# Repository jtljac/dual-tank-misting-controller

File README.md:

A circuit board design and ESPHome script for a control board responsible for a misting system for two tanks.  
A route from the pump to each tank can be enabled using solenoids attched to their labelled terminals. Powered terminals
will be indicated by an indicator LED, including when the pump is powered.

There are also a header for a Dallas 1-Wire DS18b20 waterproof temperature sensor for measuring the temperature of the 
water Tank, and a header for a HC-SR04 ultrasonic Distance sensor for use as a water level indicator. The HC-SR04 header
has an associate voltage selector header as they're supposed to be 5v but my cheap ones overheated above 3v3.

The board is powered using a 24V DC Barrel Jack and powers the pump and solenoids directly. This design has sized 
components and traces for 3A, which is generous for the required current for the ESP, pump, and two solenoids.

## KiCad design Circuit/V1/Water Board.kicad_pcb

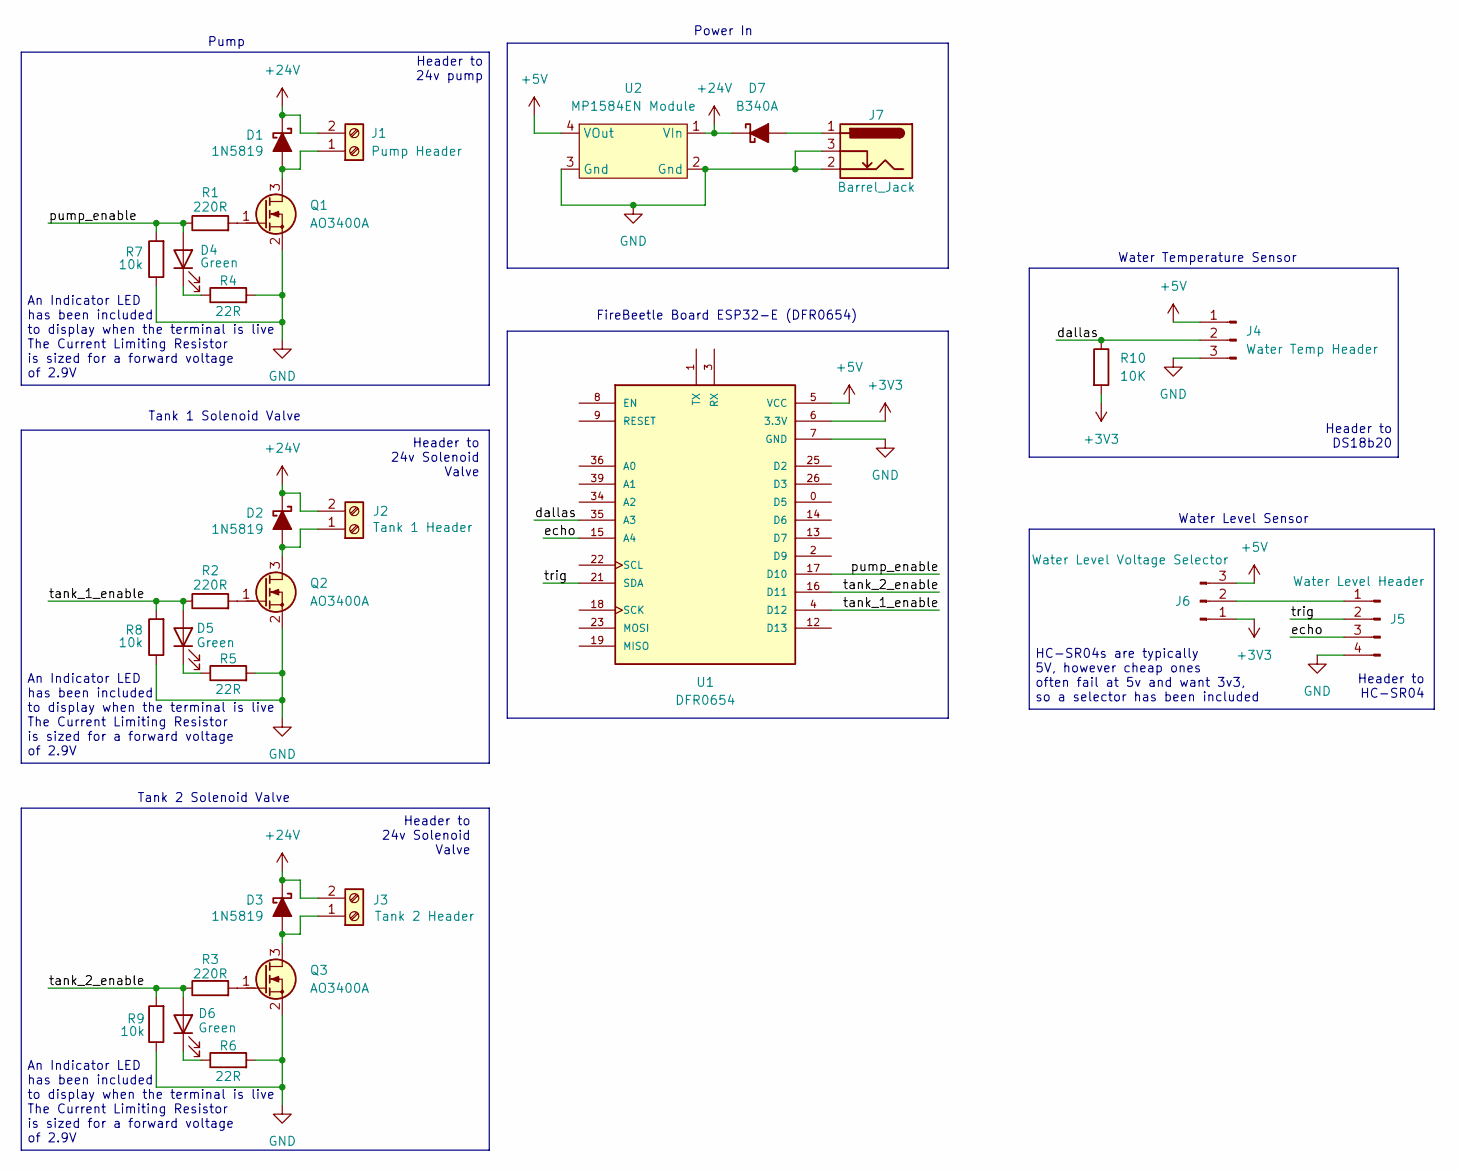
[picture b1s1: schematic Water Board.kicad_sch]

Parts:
D1, D2, D3: 1N5819; D_SOD-123
D4, D5, D6: Green; LED_0805_2012Metric_Pad1.15x1.40mm_HandSolder
D7: B340A; D_SMA_BigPads
J1: Pump Header; TerminalBlock_MAX_MX127-5.0-02P_1x02_P5.00mm
J2: Tank 1 Header; TerminalBlock_MAX_MX127-5.0-02P_1x02_P5.00mm
J3: Tank 2 Header; TerminalBlock_MAX_MX127-5.0-02P_1x02_P5.00mm
J4: Water Temp Header; PinHeader_1x03_P2.54mm_Vertical
J5: Water Level Header; PinHeader_1x04_P2.54mm_Vertical
J6: Water Level Voltage Selector; PinHeader_1x03_P2.54mm_Vertical
J7: Barrel_Jack; BarrelJack_XKB_5A
Q1, Q2, Q3: AO3400A; SOT-23_BigPads
R1, R2, R3: 220R; R_0805_2012Metric_Pad1.20x1.40mm_HandSolder
R4, R5, R6: 22R; R_0805_2012Metric_Pad1.20x1.40mm_HandSolder
R7, R8, R9: 10k; R_0805_2012Metric_Pad1.20x1.40mm_HandSolder
R10: 10K; R_0805_2012Metric_Pad1.20x1.40mm_HandSolder
U1: DFR0654; MODULE_DFR0654
U2: MP1584EN Module

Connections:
+3V3: J6.1, R10.2, U1.6 (3.3V)
+5V: J4.1, J6.3, U1.5 (VCC), U2.4 (VOut)
+24V: D1.1 (K), D2.1 (K), D3.1 (K), D7.1 (K), J1.2, J2.2, J3.2, U2.1 (VIn)
/dallas: J4.2, R10.1, U1.35 (A3)
/echo: J5.3, U1.15 (A4)
/pump_enable: D4.2 (A), R1.1, R7.2, U1.17 (D10)
/tank_1_enable: D5.2 (A), R2.1, R8.2, U1.4 (D12)
/tank_2_enable: D6.2 (A), R3.1, R9.2, U1.16 (D11)
/trig: J5.2, U1.21 (SDA)
GND: J4.3, J5.4, J7.2, J7.3, Q1.2 (S), Q2.2 (S), Q3.2 (S), R4.2, R5.2, R6.2, R7.1, R8.1, R9.1, U1.7 (GND), U2.2 (Gnd), U2.3 (Gnd); also elsewhere on the board
unnamed: D1.2 (A), J1.1, Q1.3 (D)
unnamed: D2.2 (A), J2.1, Q2.3 (D)
unnamed: D3.2 (A), J3.1, Q3.3 (D)
unnamed: D4.1 (K), R4.1
unnamed: D5.1 (K), R5.1
unnamed: D6.1 (K), R6.1
unnamed: D7.2 (A), J7.1
unnamed: J5.1, J6.2
unnamed: Q1.1 (G), R1.2
unnamed: Q2.1 (G), R2.2
unnamed: Q3.1 (G), R3.2

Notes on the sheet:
Water Level Sensor
Tank 1 Solenoid Valve
Water Temperature Sensor
An Indicator LED has been included to display when the terminal is live The Current Limiting Resistor is sized for a forward voltage of 2.9V
FireBeetle Board ESP32-E (DFR0654)
Header to HC-SR04
Power In
Header to 24v Solenoid Valve
Tank 2 Solenoid Valve
Pump
HC-SR04s are typically 5V, however cheap ones often fail at 5v and want 3v3, so a selector has been included
Header to DS18b20
Header to 24v pump

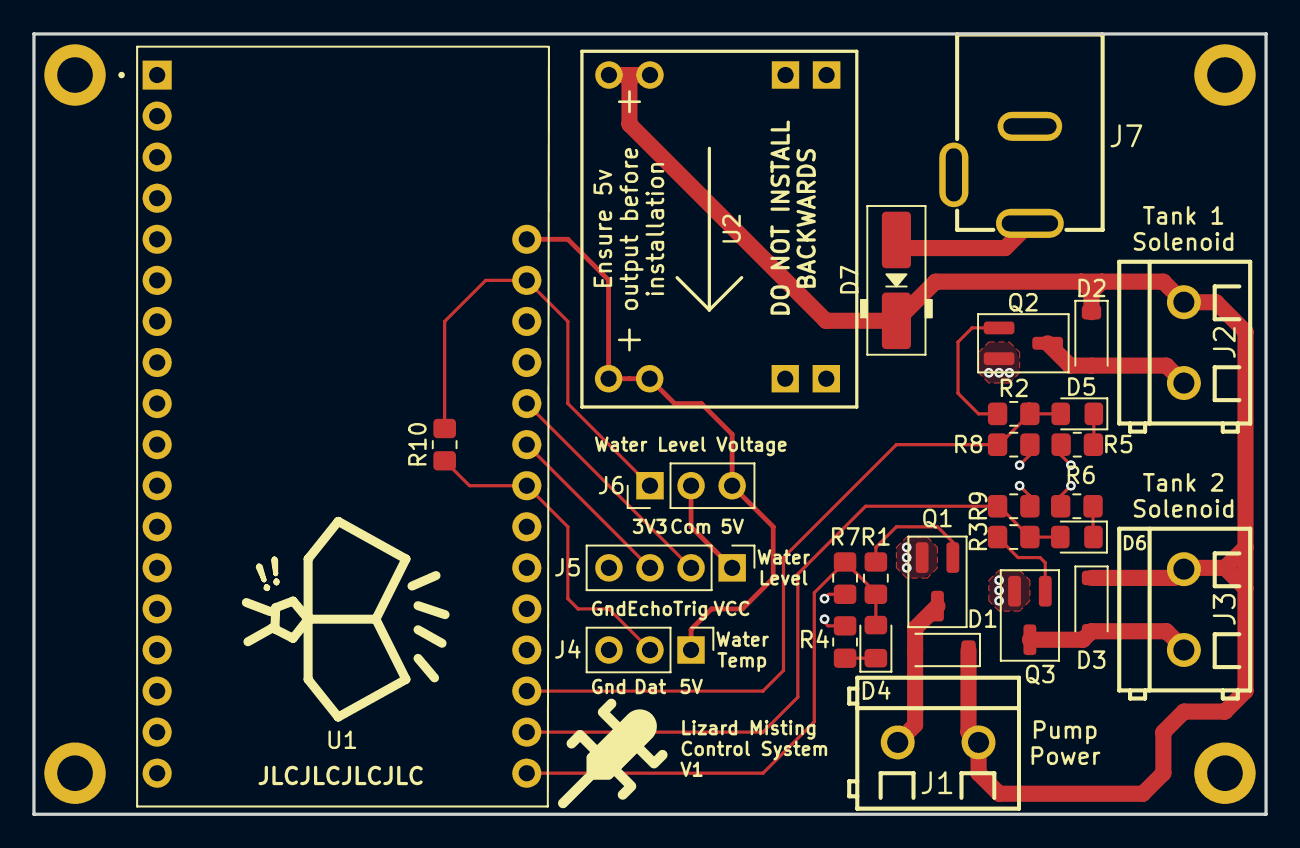
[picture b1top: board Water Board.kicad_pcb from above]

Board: 2 copper layers, 76.2 x 48.3 mm, 33 parts (0 on the bottom side), 21 nets.

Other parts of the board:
M1, M2, M3, M4: MountingHole_2.2mm_M2_DIN965_Pad

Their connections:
GND: M1.1, M2.1, M3.1, M4.1; also elsewhere on the board

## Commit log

2025-07-07 Added pull down resistors to mosfets
2025-07-08 Revise resistor and LED layout, Added preview images
